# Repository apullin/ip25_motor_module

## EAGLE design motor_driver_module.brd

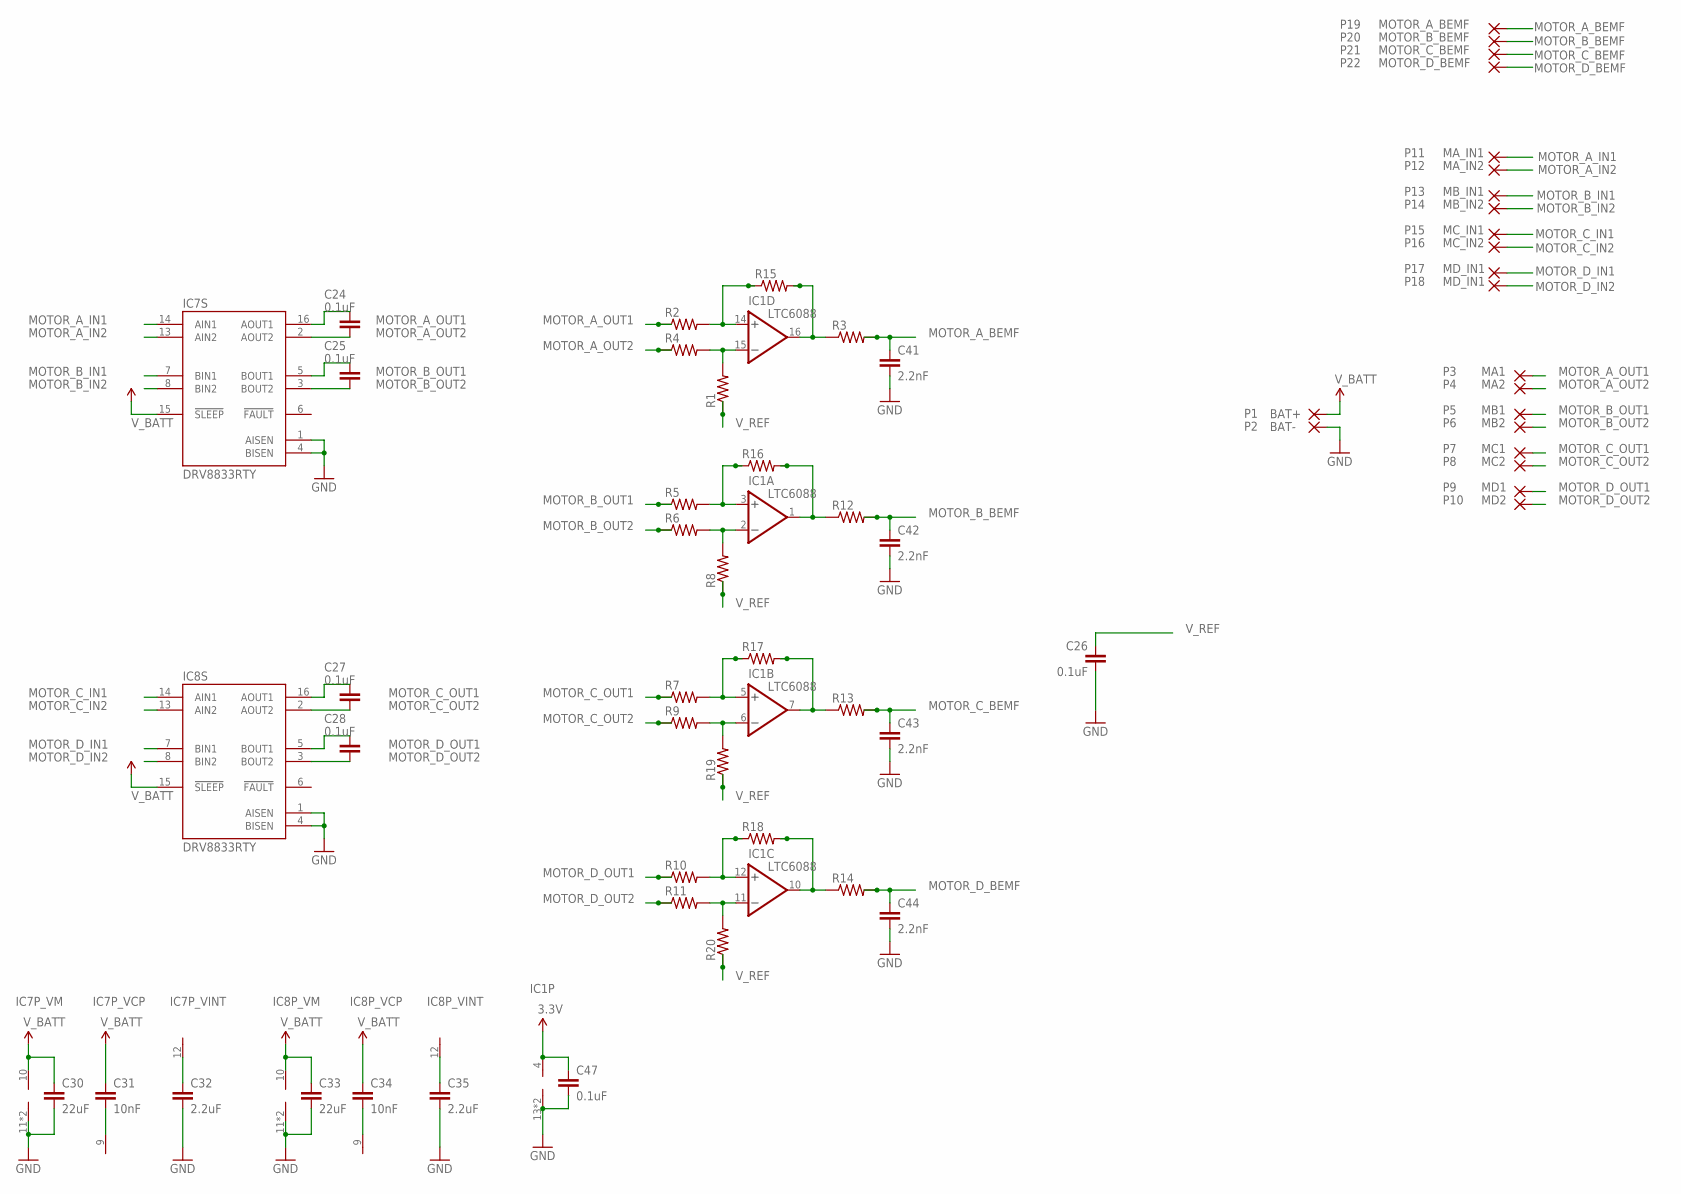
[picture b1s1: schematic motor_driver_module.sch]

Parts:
C24, C25, C27, C28: 0.1uF; 0402-CAP; VOLTAGE 10V
C26, C47: 0.1uF; 0402-CAP
C30, C33: 22uF; 0603-CAP
C31, C34: 10nF; 0402-CAP; VOLTAGE 16V
C32, C35: 2.2uF; 0402-CAP; VOLTAGE 6.3V
C41, C42, C43, C44: 2.2nF; 0402-CAP
IC1: LTC6088; DFN-16
IC7, IC8: DRV8833RTY; S-PWQFN-N16
P1: BAT+; SMD1,27-2,54
P2: BAT-; SMD1,27-2,54
P3: MA1; SMD1,27-2,54
P4: MA2; SMD1,27-2,54
P5: MB1; SMD1,27-2,54
P6: MB2; SMD1,27-2,54
P7: MC1; SMD1,27-2,54
P8: MC2; SMD1,27-2,54
P9: MD1; SMD1,27-2,54
P10: MD2; SMD1,27-2,54
P11: MA_IN1; SMD1,27-2,54
P12: MA_IN2; SMD1,27-2,54
P13: MB_IN1; SMD1,27-2,54
P14: MB_IN2; SMD1,27-2,54
P15: MC_IN1; SMD1,27-2,54
P16: MC_IN2; SMD1,27-2,54
P17, P18: MD_IN1; SMD1,27-2,54
P19: MOTOR_A_BEMF; SMD1,27-2,54
P20: MOTOR_B_BEMF; SMD1,27-2,54
P21: MOTOR_C_BEMF; SMD1,27-2,54
P22: MOTOR_D_BEMF; SMD1,27-2,54
R1, R2, R3, R4, R5, R6, R7, R8, R9, R10, R11, R12, R13, R14, R15, R16, R17, R18, R19, R20: RESISTOR0402-RES; 0402-RES

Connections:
3.3V: C47.1, IC1.4 (V+)
GND: C26.2, C30.2, C32.2, C33.2, C35.2, C41.2, C42.2, C43.2, C44.2, C47.2, IC1.13 (V-), IC1.PAD (V-), IC7.1 (AISEN), IC7.4 (BISEN), IC7.11 (V-), IC7.PPAD (V-), IC8.1 (AISEN), IC8.4 (BISEN), IC8.11 (V-), IC8.PPAD (V-), P2.1
MOTOR_A_BEMF: C41.1, P19.1, R3.2
MOTOR_A_IN1: IC7.14 (AIN1), P11.1
MOTOR_A_IN2: IC7.13 (AIN2), P12.1
MOTOR_A_OUT1: C24.1, IC7.16 (AOUT1), P3.1, R2.1
MOTOR_A_OUT2: C24.2, IC7.2 (AOUT2), P4.1, R4.1
MOTOR_B_BEMF: C42.1, P20.1, R12.2
MOTOR_B_IN1: IC7.7 (BIN1), P13.1
MOTOR_B_IN2: IC7.8 (BIN2), P14.1
MOTOR_B_OUT1: C25.1, IC7.5 (BOUT1), P5.1, R5.1
MOTOR_B_OUT2: C25.2, IC7.3 (BOUT2), P6.1, R6.1
MOTOR_C_BEMF: C43.1, P21.1, R13.2
MOTOR_C_IN1: IC8.14 (AIN1), P15.1
MOTOR_C_IN2: IC8.13 (AIN2), P16.1
MOTOR_C_OUT1: C27.1, IC8.16 (AOUT1), P7.1, R7.1
MOTOR_C_OUT2: C27.2, IC8.2 (AOUT2), P8.1, R9.1
MOTOR_D_BEMF: C44.1, P22.1, R14.2
MOTOR_D_IN1: IC8.7 (BIN1), P17.1
MOTOR_D_IN2: IC8.8 (BIN2), P18.1
MOTOR_D_OUT1: C28.1, IC8.5 (BOUT1), P9.1, R10.1
MOTOR_D_OUT2: C28.2, IC8.3 (BOUT2), P10.1, R11.1
unnamed: C31.2, IC7.9 (V+)
unnamed: C32.1, IC7.12 (V-)
unnamed: C34.2, IC8.9 (V+)
unnamed: C35.1, IC8.12 (V-)
unnamed: IC1.3 (+IN), R5.2, R16.1
unnamed: IC1.2 (-IN), R6.2, R8.2
unnamed: IC1.5 (+IN), R7.2, R17.1
unnamed: IC1.6 (-IN), R9.2, R19.2
unnamed: IC1.12 (+IN), R10.2, R18.1
unnamed: IC1.11 (-IN), R11.2, R20.2
unnamed: IC1.14 (+IN), R2.2, R15.1
unnamed: IC1.15 (-IN), R1.2, R4.2
unnamed: IC1.10 (OUT), R14.1, R18.2
unnamed: IC1.7 (OUT), R13.1, R17.2
unnamed: IC1.16 (OUT), R3.1, R15.2
unnamed: IC1.1 (OUT), R12.1, R16.2
V_BATT: C30.1, C31.1, C33.1, C34.1, IC7.10 (V+), IC7.15 (!SLEEP), IC8.10 (V+), IC8.15 (!SLEEP), P1.1
V_REF: C26.1, R1.1, R8.1, R19.1, R20.1

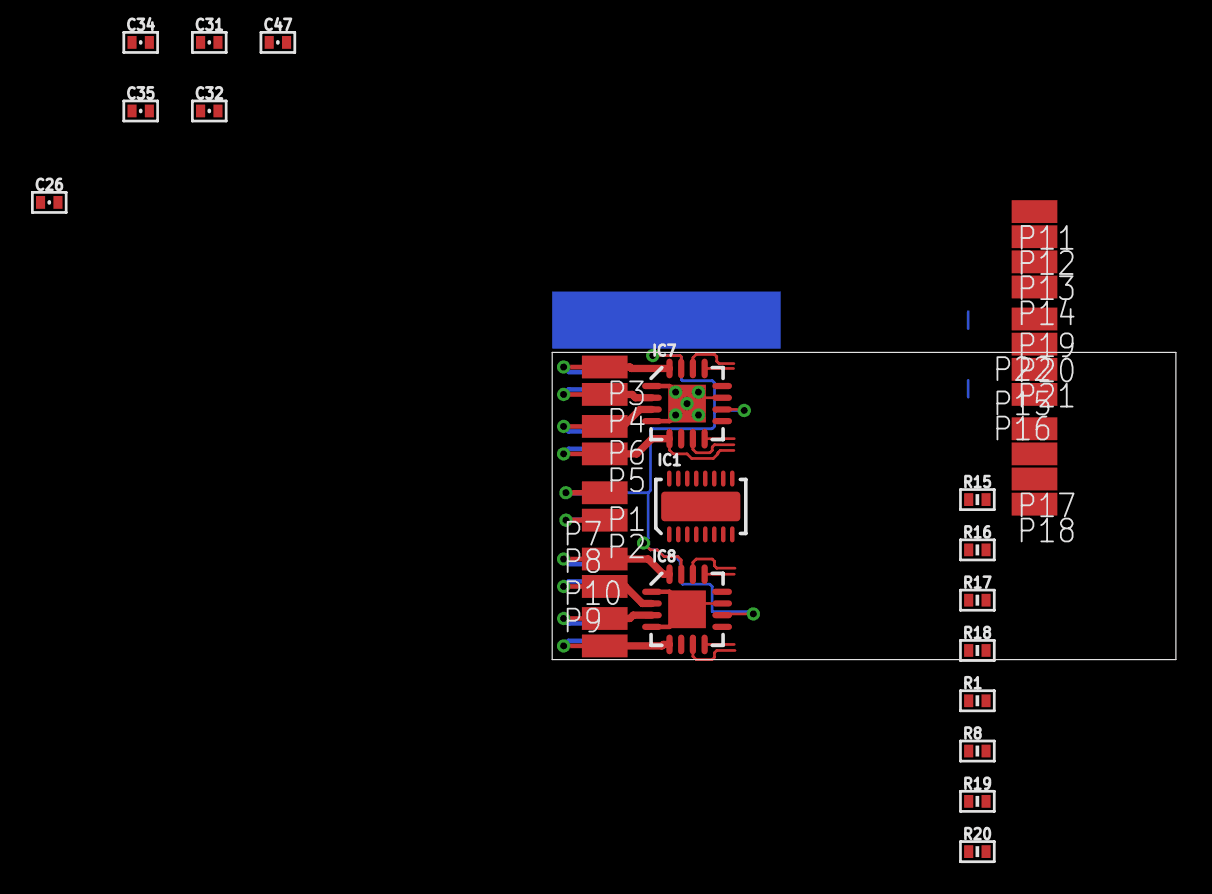
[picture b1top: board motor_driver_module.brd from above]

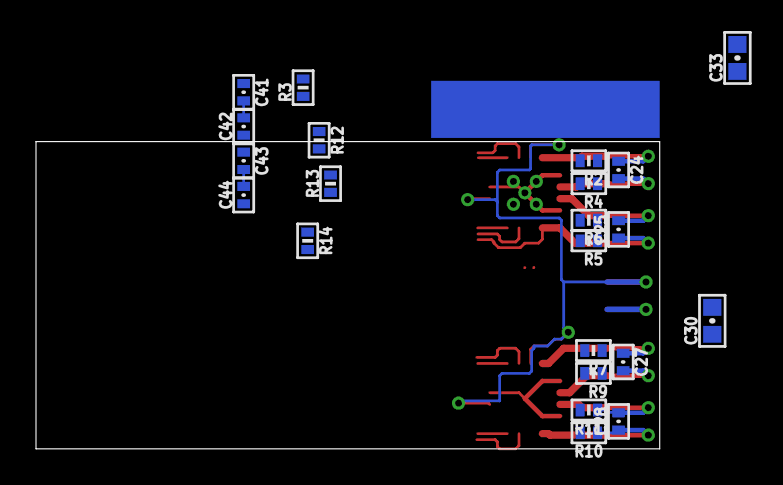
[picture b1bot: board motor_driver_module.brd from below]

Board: 2 copper layers, 34.7 x 17.1 mm, 61 parts (22 on the bottom side), 40 nets.

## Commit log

2014-08-21 Initial commit of files and .gitignore
2014-08-21 Fixed .b#* ignore in .gitignore
2014-08-21 Further routing for super space efficiency.
2014-08-22 More rerouting. Minimal size does not look promising as of right now.
2014-08-22 Appears more promising to use LTC6088 and discrete resistors.
2014-08-25 More routing. No progress.
2014-08-25 Further routing. No progress.

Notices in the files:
parts and their libraries:
biomimetic: UC Regents. All rights reserved.
